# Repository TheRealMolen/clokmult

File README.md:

#  k l ø k k e n f ä n g l e r

to build & upload this:

* reset pico into bootloader _(new drive should appear, let's say `D:`)_
* open folder in vs code
* head to terminal
* `vcsetup.bat`
* `cd build`
* `nmake && cp clokmult/clokmult.uf2 d:\`

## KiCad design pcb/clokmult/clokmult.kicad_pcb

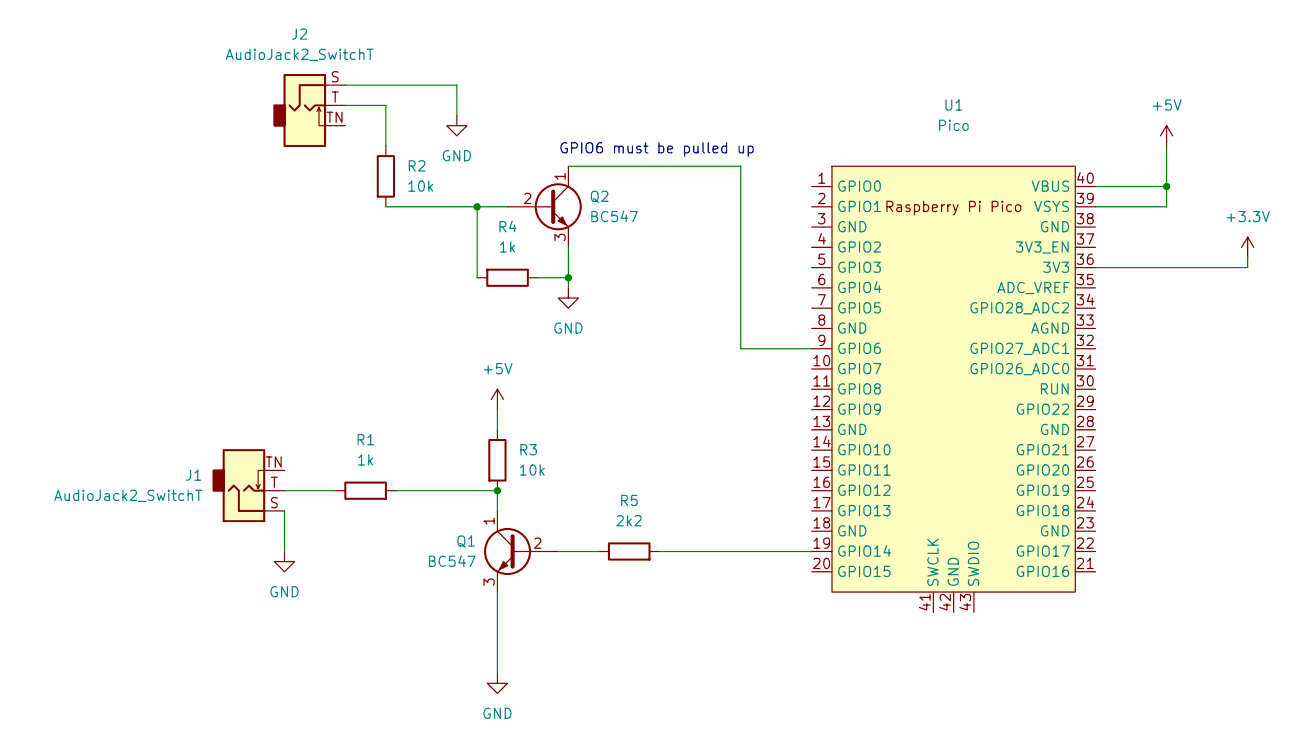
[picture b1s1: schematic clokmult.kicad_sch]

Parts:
J1, J2: AudioJack2_SwitchT; Jack_3.5mm_QingPu_WQP-PJ398SM_Vertical
Q1, Q2: BC547; TO-92_Inline
R1, R4: 1k; R_Axial_DIN0207_L6.3mm_D2.5mm_P10.16mm_Horizontal
R2, R3: 10k; R_Axial_DIN0207_L6.3mm_D2.5mm_P10.16mm_Horizontal
R5: 2k2; R_Axial_DIN0207_L6.3mm_D2.5mm_P10.16mm_Horizontal
U1: Pico; RPi_Pico_SMD_TH

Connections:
+3.3V: U1.36 (3V3)
+5V: R3.1, U1.39 (VSYS), U1.40 (VBUS)
GND: J1.S, J2.S, Q1.3 (E), Q2.3 (E), R4.1
unnamed: J1.T, R1.1
unnamed: J2.T, R2.1
unnamed: Q1.1 (C), R1.2, R3.2
unnamed: Q1.2 (B), R5.1
unnamed: Q2.1 (C), U1.9 (GPIO6)
unnamed: Q2.2 (B), R2.2, R4.2
unnamed: R5.2, U1.19 (GPIO14)

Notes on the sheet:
GPIO6 must be pulled up

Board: 2 copper layers, 10 parts (0 on the bottom side), 9 nets, no tracks yet.

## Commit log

2023-08-20 add wip pcb
2023-08-20 added 7segment
2023-08-20 stop the downstream clocks when the upstream stops
